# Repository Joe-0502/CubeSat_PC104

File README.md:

# CubeSat_PC104

Symbol and footprint libaraies in KiCAD need to be changed.

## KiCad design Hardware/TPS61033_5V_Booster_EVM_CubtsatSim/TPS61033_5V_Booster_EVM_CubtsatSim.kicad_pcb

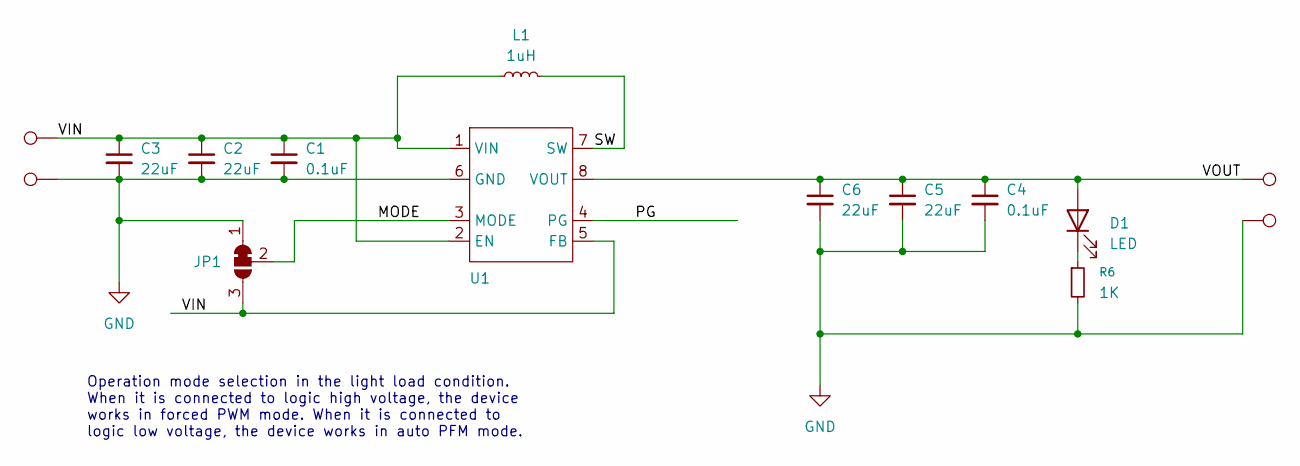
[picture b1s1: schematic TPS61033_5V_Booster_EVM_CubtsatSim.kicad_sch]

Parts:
C1, C4: 0.1uF; C_0603_1608Metric_Pad1.08x0.95mm_HandSolder
C2, C3, C5, C6: 22uF; C_0603_1608Metric_Pad1.08x0.95mm_HandSolder
D1: LED; LED_0603_1608Metric
JP1: SolderJumper_3_Bridged12; SolderJumper-3_P1.3mm_Open_RoundedPad1.0x1.5mm
L1: 1uH; IND_EXLA-0402_EAT
R6: 1K; R_0603_1608Metric_Pad0.98x0.95mm_HandSolder
TP1, TP2, TP3, TP4: TestPoint; TestPoint_THTPad_1.5x1.5mm_Drill0.7mm
U1: SOT-5X3

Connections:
/MODE: JP1.2 (C), U1.3 (MODE)
/PG: U1.4 (PG)
/SW: L1.2, U1.7 (SW)
/VIN: C1.1, C2.1, C3.1, JP1.3 (B), L1.1, TP1.1, U1.1 (VIN), U1.2 (EN), U1.5 (FB)
/VOUT: C4.1, C5.1, C6.1, D1.2 (A), TP3.1, U1.8 (VOUT)
GND: C1.2, C2.2, C3.2, C4.2, C5.2, C6.2, JP1.1 (A), R6.2, TP2.1, TP4.1, U1.6 (GND)
unnamed: D1.1 (K), R6.1

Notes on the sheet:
Operation mode selection in the light load condition. When it is connected to logic high voltage, the device works in forced PWM mode. When it is connected to logic low voltage, the device works in auto PFM mode.

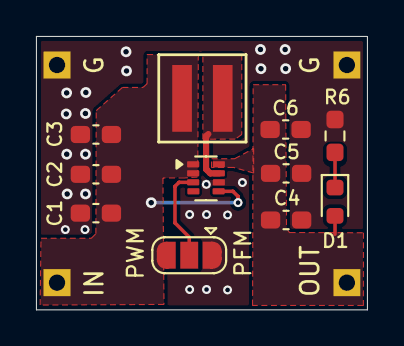
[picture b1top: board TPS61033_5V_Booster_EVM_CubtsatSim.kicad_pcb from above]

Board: 2 copper layers, 18.4 x 15.2 mm, 15 parts (0 on the bottom side), 6 nets.

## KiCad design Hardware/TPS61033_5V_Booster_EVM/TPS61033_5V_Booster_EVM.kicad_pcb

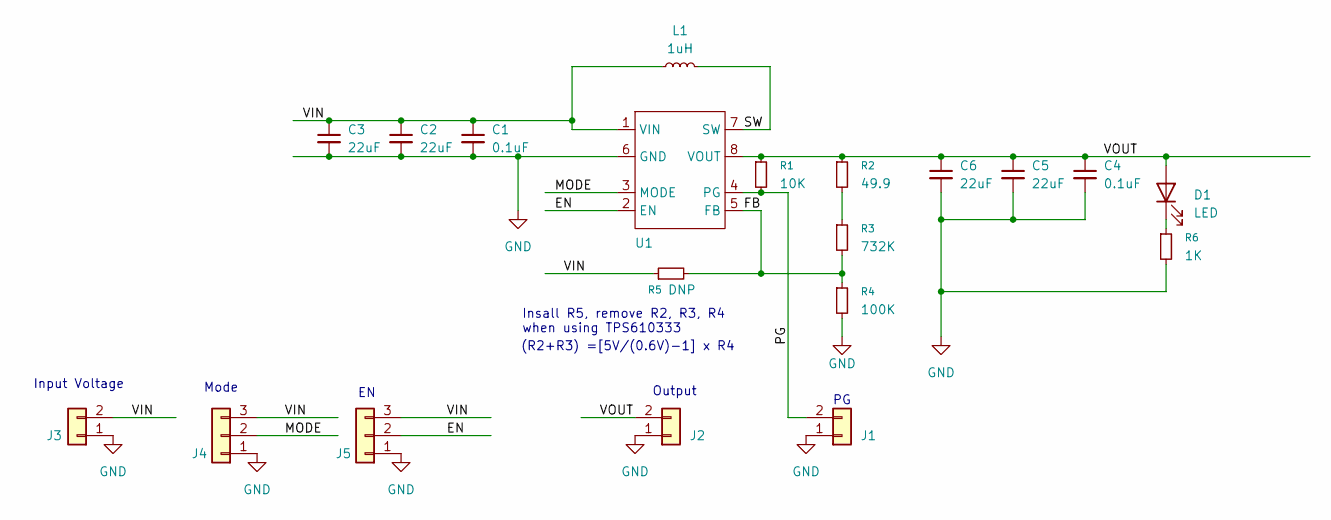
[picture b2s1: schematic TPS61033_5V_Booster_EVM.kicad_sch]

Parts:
C1, C4: 0.1uF; C_0805_2012Metric_Pad1.18x1.45mm_HandSolder
C2, C3, C5, C6: 22uF; C_0805_2012Metric_Pad1.18x1.45mm_HandSolder
D1: LED; LED_0603_1608Metric
J1, J2, J3: Conn_01x02; PinHeader_1x02_P2.54mm_Vertical
J4, J5: Conn_01x03; PinHeader_1x03_P2.54mm_Vertical
L1: 1uH; IND_EXLA-0402_EAT
R1: 10K; R_0603_1608Metric_Pad0.98x0.95mm_HandSolder
R2: 49.9; R_0603_1608Metric_Pad0.98x0.95mm_HandSolder
R3: 732K; R_0603_1608Metric_Pad0.98x0.95mm_HandSolder
R4: 100K; R_0603_1608Metric_Pad0.98x0.95mm_HandSolder
R5: DNP; R_0603_1608Metric_Pad0.98x0.95mm_HandSolder
R6: 1K; R_0603_1608Metric_Pad0.98x0.95mm_HandSolder
U1: SOT-5X3

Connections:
/EN: J5.2, U1.2 (EN)
/FB: R3.2, R4.1, R5.2, U1.5 (FB)
/MODE: J4.2, U1.3 (MODE)
/PG: J1.2, R1.2, U1.4 (PG)
/SW: L1.2, U1.7 (SW)
/VIN: C1.1, C2.1, C3.1, J3.2, J4.3, J5.3, L1.1, R5.1, U1.1 (VIN)
/VOUT: C4.1, C5.1, C6.1, D1.2 (A), J2.2, R1.1, R2.1, U1.8 (VOUT)
GND: C1.2, C2.2, C3.2, C4.2, C5.2, C6.2, J1.1, J2.1, J3.1, J4.1, J5.1, R4.2, R6.2, U1.6 (GND)
unnamed: D1.1 (K), R6.1
unnamed: R2.2, R3.1

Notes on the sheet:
(R2+R3) =[5V/(0.6V)-1] x R4
Output
Insall R5, remove R2, R3, R4 when using TPS610333
Input Voltage
Mode

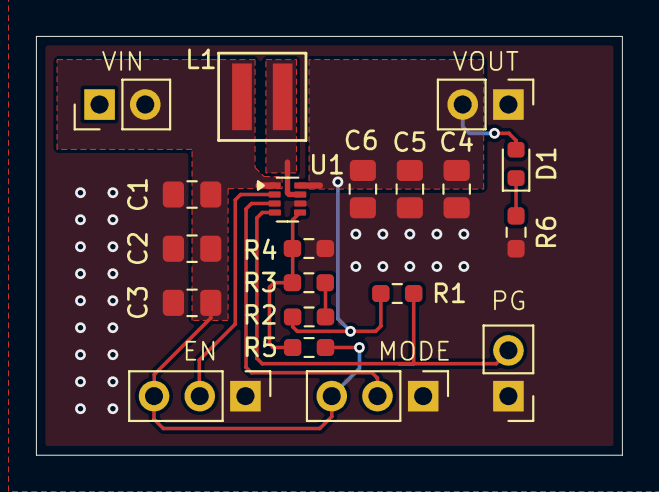
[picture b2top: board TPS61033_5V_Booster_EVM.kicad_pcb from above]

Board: 2 copper layers, 32.6 x 23.3 mm, 20 parts (0 on the bottom side), 10 nets.

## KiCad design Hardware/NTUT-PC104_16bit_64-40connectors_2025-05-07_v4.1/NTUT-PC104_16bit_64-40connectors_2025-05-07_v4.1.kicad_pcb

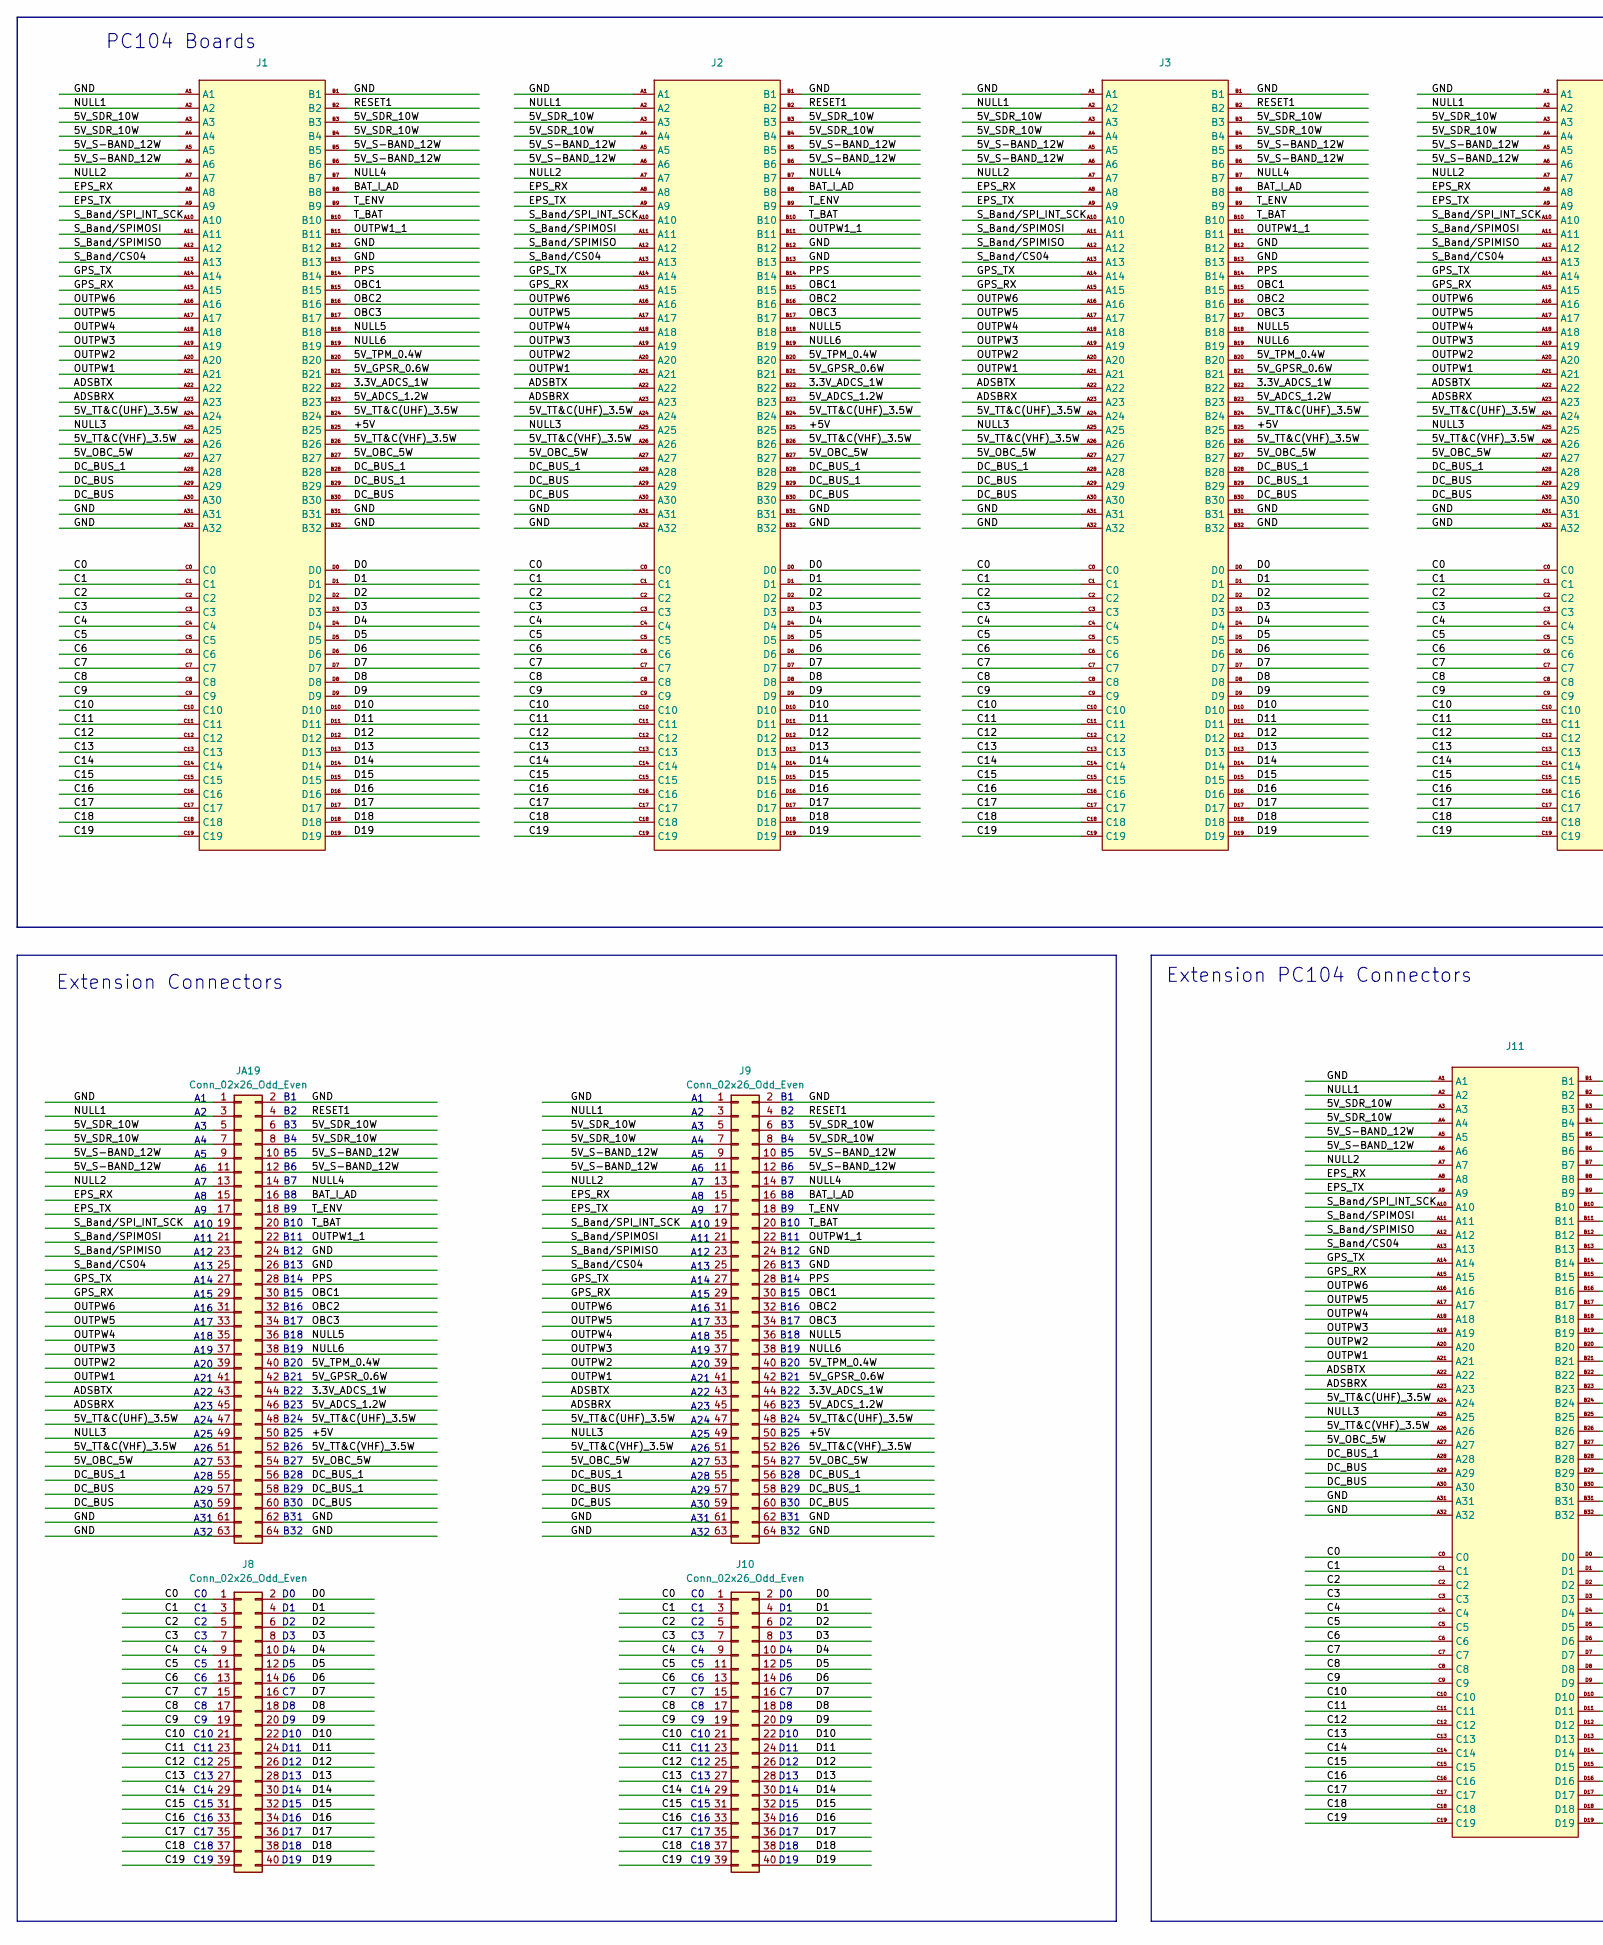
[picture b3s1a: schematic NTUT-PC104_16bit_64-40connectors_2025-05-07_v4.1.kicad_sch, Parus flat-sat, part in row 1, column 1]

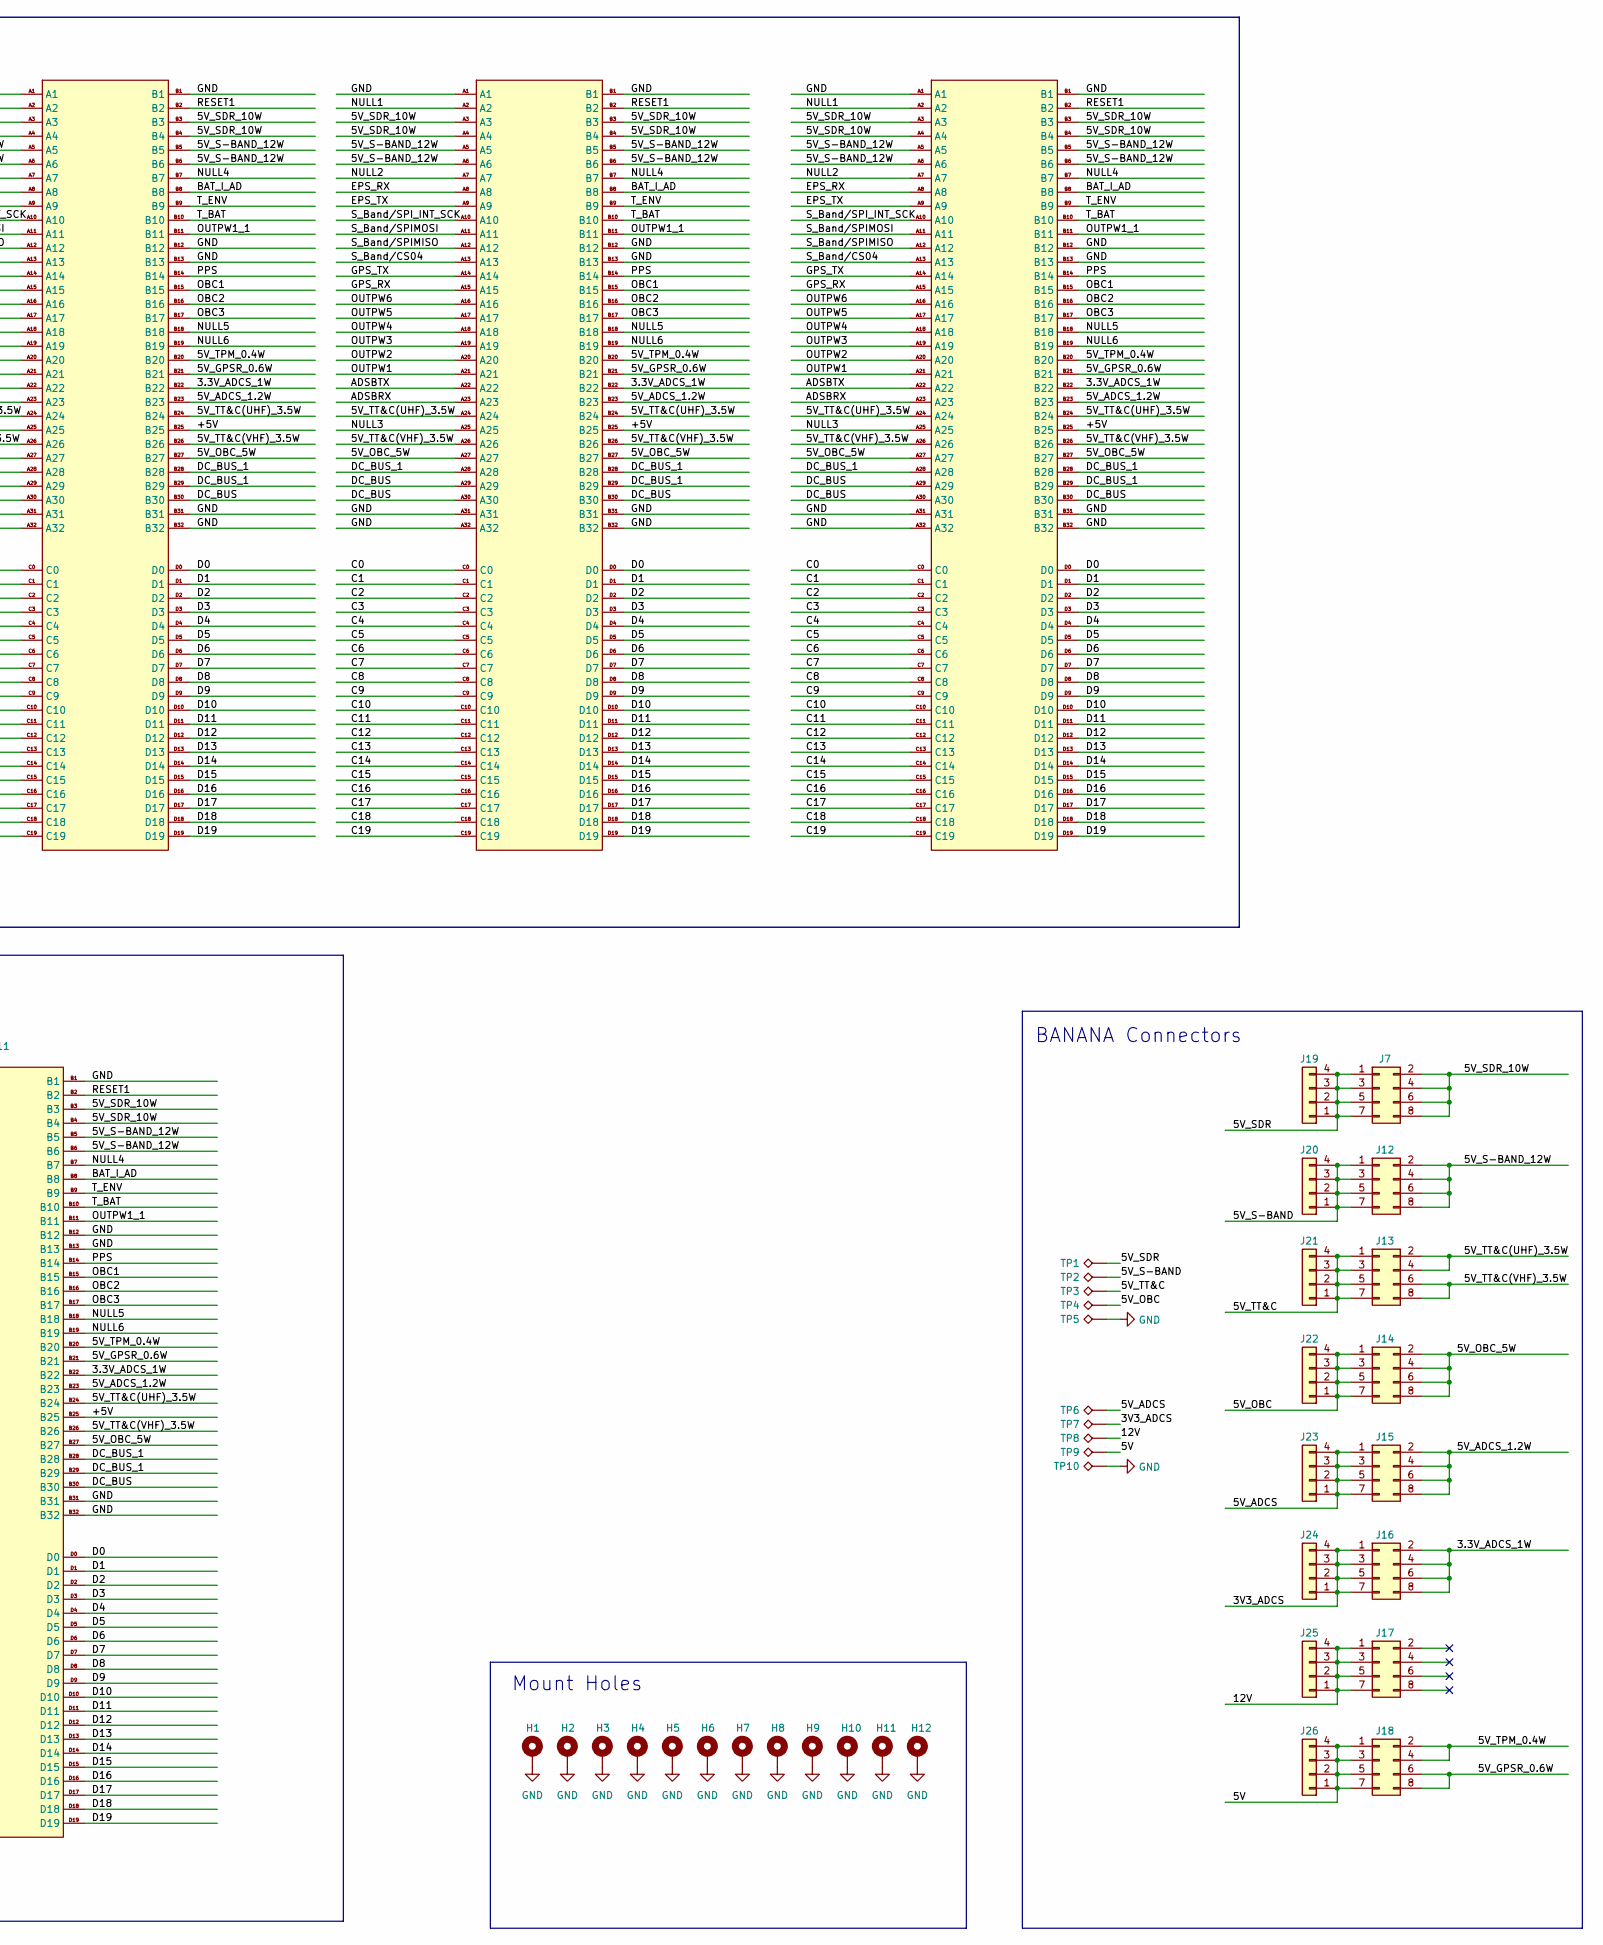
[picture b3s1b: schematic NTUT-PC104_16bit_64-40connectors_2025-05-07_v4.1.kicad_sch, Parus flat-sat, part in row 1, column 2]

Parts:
H1, H2, H3, H4, H5, H6, H7, H8, H9, H10, H11, H12: MountingHole_Pad; MountingHole_3.2mm_M3_Pad_Via
J1, J2, J3, J4, J5, J6: CubeSat_PC104_16bit_footprint
J7, J12, J13, J14, J15, J16, J17, J18: Conn_02x04_Odd_Even; PinHeader_2x04_P2.54mm_Vertical
J8, J10: Conn_02x26_Odd_Even; PinHeader_2x20_P2.54mm_Vertical
J9: Conn_02x26_Odd_Even; PinHeader_2x32_P2.54mm_Vertical
J11: PC104_16bit_Connector
J19, J20, J21, J22, J23, J24, J25, J26: Conn_01x04; PinHeader_1x04_P2.54mm_Vertical
JA19: Conn_02x26_Odd_Even; PinHeader_2x32_P2.54mm_Vertical
TP1, TP2, TP3, TP4, TP5, TP6, TP7, TP8, TP9, TP10: TestPoint_Alt; KSE_PN6095

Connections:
/3.3V_ADCS_1W: J1.B22, J2.B22, J3.B22, J4.B22, J5.B22, J6.B22, J9.44, J11.B22, J16.2, J16.4, J16.6, J16.8, JA19.44
/3V3_ADCS: J16.1, J16.3, J16.5, J16.7, J24.1, J24.2, J24.3, J24.4, TP7.1
/5V: J18.1, J18.3, J18.5, J18.7, J26.1, J26.2, J26.3, J26.4, TP9.1
/5V_ADCS: J15.1, J15.3, J15.5, J15.7, J23.1, J23.2, J23.3, J23.4, TP6.1
/5V_ADCS_1.2W: J1.B23, J2.B23, J3.B23, J4.B23, J5.B23, J6.B23, J9.46, J11.B23, J15.2, J15.4, J15.6, J15.8, JA19.46
/5V_GPSR_0.6W: J1.B21, J2.B21, J3.B21, J4.B21, J5.B21, J6.B21, J9.42, J11.B21, J18.6, J18.8, JA19.42
/5V_OBC: J14.1, J14.3, J14.5, J14.7, J22.1, J22.2, J22.3, J22.4, TP4.1
/5V_OBC_5W: J1.A27, J1.B27, J2.A27, J2.B27, J3.A27, J3.B27, J4.A27, J4.B27, J5.A27, J5.B27, J6.A27, J6.B27, J9.53, J9.54, J11.A27, J11.B27, J14.2, J14.4, J14.6, J14.8, JA19.53, JA19.54
/5V_S-BAND: J12.1, J12.3, J12.5, J12.7, J20.1, J20.2, J20.3, J20.4, TP2.1
/5V_S-BAND_12W: J1.A5, J1.A6, J1.B5, J1.B6, J2.A5, J2.A6, J2.B5, J2.B6, J3.A5, J3.A6, J3.B5, J3.B6, J4.A5, J4.A6, J4.B5, J4.B6, J5.A5, J5.A6, J5.B5, J5.B6, J6.A5, J6.A6, J6.B5, J6.B6, J9.9, J9.10, J9.11, J9.12, J11.A5, J11.A6, J11.B5, J11.B6, J12.2, J12.4, J12.6, J12.8, JA19.9, JA19.10, JA19.11, JA19.12
/5V_SDR: J7.1, J7.3, J7.5, J7.7, J19.1, J19.2, J19.3, J19.4, TP1.1
/5V_SDR_10W: J1.A3, J1.A4, J1.B3, J1.B4, J2.A3, J2.A4, J2.B3, J2.B4, J3.A3, J3.A4, J3.B3, J3.B4, J4.A3, J4.A4, J4.B3, J4.B4, J5.A3, J5.A4, J5.B3, J5.B4, J6.A3, J6.A4, J6.B3, J6.B4, J7.2, J7.4, J7.6, J7.8, J9.5, J9.6, J9.7, J9.8, J11.A3, J11.A4, J11.B3, J11.B4, JA19.5, JA19.6, JA19.7, JA19.8
/5V_TPM_0.4W: J1.B20, J2.B20, J3.B20, J4.B20, J5.B20, J6.B20, J9.40, J11.B20, J18.2, J18.4, JA19.40
/5V_TT&C: J13.1, J13.3, J13.5, J13.7, J21.1, J21.2, J21.3, J21.4, TP3.1
/5V_TT&C(UHF)_3.5W: J1.A24, J1.B24, J2.A24, J2.B24, J3.A24, J3.B24, J4.A24, J4.B24, J5.A24, J5.B24, J6.A24, J6.B24, J9.47, J9.48, J11.A24, J11.B24, J13.2, J13.4, JA19.47, JA19.48
/5V_TT&C(VHF)_3.5W: J1.A26, J1.B26, J2.A26, J2.B26, J3.A26, J3.B26, J4.A26, J4.B26, J5.A26, J5.B26, J6.A26, J6.B26, J9.51, J9.52, J11.A26, J11.B26, J13.6, J13.8, JA19.51, JA19.52
/12V: J17.1, J17.3, J17.5, J17.7, J25.1, J25.2, J25.3, J25.4, TP8.1
/+5V: J1.B25, J2.B25, J3.B25, J4.B25, J5.B25, J6.B25, J9.50, J11.B25, JA19.50
/ADSBRX: J1.A23, J2.A23, J3.A23, J4.A23, J5.A23, J6.A23, J9.45, J11.A23, JA19.45
/ADSBTX: J1.A22, J2.A22, J3.A22, J4.A22, J5.A22, J6.A22, J9.43, J11.A22, JA19.43
/BAT_I_AD: J1.B8, J2.B8, J3.B8, J4.B8, J5.B8, J6.B8, J9.16, J11.B8, JA19.16
/C0: J1.C0, J2.C0, J3.C0, J4.C0, J5.C0, J6.C0, J8.1, J10.1, J11.C0
/C1: J1.C1, J2.C1, J3.C1, J4.C1, J5.C1, J6.C1, J8.3, J10.3, J11.C1
/C2: J1.C2, J2.C2, J3.C2, J4.C2, J5.C2, J6.C2, J8.5, J10.5, J11.C2
/C3: J1.C3, J2.C3, J3.C3, J4.C3, J5.C3, J6.C3, J8.7, J10.7, J11.C3
/C4: J1.C4, J2.C4, J3.C4, J4.C4, J5.C4, J6.C4, J8.9, J10.9, J11.C4
/C5: J1.C5, J2.C5, J3.C5, J4.C5, J5.C5, J6.C5, J8.11, J10.11, J11.C5
/C6: J1.C6, J2.C6, J3.C6, J4.C6, J5.C6, J6.C6, J8.13, J10.13, J11.C6
/C7: J1.C7, J2.C7, J3.C7, J4.C7, J5.C7, J6.C7, J8.15, J10.15, J11.C7
/C8: J1.C8, J2.C8, J3.C8, J4.C8, J5.C8, J6.C8, J8.17, J10.17, J11.C8
/C9: J1.C9, J2.C9, J3.C9, J4.C9, J5.C9, J6.C9, J8.19, J10.19, J11.C9
/C10: J1.C10, J2.C10, J3.C10, J4.C10, J5.C10, J6.C10, J8.21, J10.21, J11.C10
/C11: J1.C11, J2.C11, J3.C11, J4.C11, J5.C11, J6.C11, J8.23, J10.23, J11.C11
/C12: J1.C12, J2.C12, J3.C12, J4.C12, J5.C12, J6.C12, J8.25, J10.25, J11.C12
/C13: J1.C13, J2.C13, J3.C13, J4.C13, J5.C13, J6.C13, J8.27, J10.27, J11.C13
/C14: J1.C14, J2.C14, J3.C14, J4.C14, J5.C14, J6.C14, J8.29, J10.29, J11.C14
/C15: J1.C15, J2.C15, J3.C15, J4.C15, J5.C15, J6.C15, J8.31, J10.31, J11.C15
/C16: J1.C16, J2.C16, J3.C16, J4.C16, J5.C16, J6.C16, J8.33, J10.33, J11.C16
/C17: J1.C17, J2.C17, J3.C17, J4.C17, J5.C17, J6.C17, J8.35, J10.35, J11.C17
/C18: J1.C18, J2.C18, J3.C18, J4.C18, J5.C18, J6.C18, J8.37, J10.37, J11.C18
/C19: J1.C19, J2.C19, J3.C19, J4.C19, J5.C19, J6.C19, J8.39, J10.39, J11.C19
/D0: J1.D0, J2.D0, J3.D0, J4.D0, J5.D0, J6.D0, J8.2, J10.2, J11.D0
/D1: J1.D1, J2.D1, J3.D1, J4.D1, J5.D1, J6.D1, J8.4, J10.4, J11.D1
/D2: J1.D2, J2.D2, J3.D2, J4.D2, J5.D2, J6.D2, J8.6, J10.6, J11.D2
/D3: J1.D3, J2.D3, J3.D3, J4.D3, J5.D3, J6.D3, J8.8, J10.8, J11.D3
/D4: J1.D4, J2.D4, J3.D4, J4.D4, J5.D4, J6.D4, J8.10, J10.10, J11.D4
/D5: J1.D5, J2.D5, J3.D5, J4.D5, J5.D5, J6.D5, J8.12, J10.12, J11.D5
/D6: J1.D6, J2.D6, J3.D6, J4.D6, J5.D6, J6.D6, J8.14, J10.14, J11.D6
/D7: J1.D7, J2.D7, J3.D7, J4.D7, J5.D7, J6.D7, J8.16, J10.16, J11.D7
/D8: J1.D8, J2.D8, J3.D8, J4.D8, J5.D8, J6.D8, J8.18, J10.18, J11.D8
/D9: J1.D9, J2.D9, J3.D9, J4.D9, J5.D9, J6.D9, J8.20, J10.20, J11.D9
/D10: J1.D10, J2.D10, J3.D10, J4.D10, J5.D10, J6.D10, J8.22, J10.22, J11.D10
/D11: J1.D11, J2.D11, J3.D11, J4.D11, J5.D11, J6.D11, J8.24, J10.24, J11.D11
/D12: J1.D12, J2.D12, J3.D12, J4.D12, J5.D12, J6.D12, J8.26, J10.26, J11.D12
/D13: J1.D13, J2.D13, J3.D13, J4.D13, J5.D13, J6.D13, J8.28, J10.28, J11.D13
/D14: J1.D14, J2.D14, J3.D14, J4.D14, J5.D14, J6.D14, J8.30, J10.30, J11.D14
/D15: J1.D15, J2.D15, J3.D15, J4.D15, J5.D15, J6.D15, J8.32, J10.32, J11.D15
/D16: J1.D16, J2.D16, J3.D16, J4.D16, J5.D16, J6.D16, J8.34, J10.34, J11.D16
/D17: J1.D17, J2.D17, J3.D17, J4.D17, J5.D17, J6.D17, J8.36, J10.36, J11.D17
/D18: J1.D18, J2.D18, J3.D18, J4.D18, J5.D18, J6.D18, J8.38, J10.38, J11.D18
/D19: J1.D19, J2.D19, J3.D19, J4.D19, J5.D19, J6.D19, J8.40, J10.40, J11.D19
/DC_BUS: J1.A29, J1.A30, J1.B30, J2.A29, J2.A30, J2.B30, J3.A29, J3.A30, J3.B30, J4.A29, J4.A30, J4.B30, J5.A29, J5.A30, J5.B30, J6.A29, J6.A30, J6.B30, J9.57, J9.59, J9.60, J11.A29, J11.A30, J11.B30, JA19.57, JA19.59, JA19.60
/DC_BUS_1: J1.A28, J1.B28, J1.B29, J2.A28, J2.B28, J2.B29, J3.A28, J3.B28, J3.B29, J4.A28, J4.B28, J4.B29, J5.A28, J5.B28, J5.B29, J6.A28, J6.B28, J6.B29, J9.55, J9.56, J9.58, J11.A28, J11.B28, J11.B29, JA19.55, JA19.56, JA19.58
/EPS_RX: J1.A8, J2.A8, J3.A8, J4.A8, J5.A8, J6.A8, J9.15, J11.A8, JA19.15
/EPS_TX: J1.A9, J2.A9, J3.A9, J4.A9, J5.A9, J6.A9, J9.17, J11.A9, JA19.17
/GPS_RX: J1.A15, J2.A15, J3.A15, J4.A15, J5.A15, J6.A15, J9.29, J11.A15, JA19.29
/GPS_TX: J1.A14, J2.A14, J3.A14, J4.A14, J5.A14, J6.A14, J9.27, J11.A14, JA19.27
/NULL1: J1.A2, J2.A2, J3.A2, J4.A2, J5.A2, J6.A2, J9.3, J11.A2, JA19.3
/NULL2: J1.A7, J2.A7, J3.A7, J4.A7, J5.A7, J6.A7, J9.13, J11.A7, JA19.13
/NULL3: J1.A25, J2.A25, J3.A25, J4.A25, J5.A25, J6.A25, J9.49, J11.A25, JA19.49
/NULL4: J1.B7, J2.B7, J3.B7, J4.B7, J5.B7, J6.B7, J9.14, J11.B7, JA19.14
/NULL5: J1.B18, J2.B18, J3.B18, J4.B18, J5.B18, J6.B18, J9.36, J11.B18, JA19.36
/NULL6: J1.B19, J2.B19, J3.B19, J4.B19, J5.B19, J6.B19, J9.38, J11.B19, JA19.38
/OBC1: J1.B15, J2.B15, J3.B15, J4.B15, J5.B15, J6.B15, J9.30, J11.B15, JA19.30
/OBC2: J1.B16, J2.B16, J3.B16, J4.B16, J5.B16, J6.B16, J9.32, J11.B16, JA19.32
/OBC3: J1.B17, J2.B17, J3.B17, J4.B17, J5.B17, J6.B17, J9.34, J11.B17, JA19.34
/OUTPW1: J1.A21, J2.A21, J3.A21, J4.A21, J5.A21, J6.A21, J9.41, J11.A21, JA19.41
/OUTPW1_1: J1.B11, J2.B11, J3.B11, J4.B11, J5.B11, J6.B11, J9.22, J11.B11, JA19.22
/OUTPW2: J1.A20, J2.A20, J3.A20, J4.A20, J5.A20, J6.A20, J9.39, J11.A20, JA19.39
/OUTPW3: J1.A19, J2.A19, J3.A19, J4.A19, J5.A19, J6.A19, J9.37, J11.A19, JA19.37
/OUTPW4: J1.A18, J2.A18, J3.A18, J4.A18, J5.A18, J6.A18, J9.35, J11.A18, JA19.35
/OUTPW5: J1.A17, J2.A17, J3.A17, J4.A17, J5.A17, J6.A17, J9.33, J11.A17, JA19.33
/OUTPW6: J1.A16, J2.A16, J3.A16, J4.A16, J5.A16, J6.A16, J9.31, J11.A16, JA19.31
/PPS: J1.B14, J2.B14, J3.B14, J4.B14, J5.B14, J6.B14, J9.28, J11.B14, JA19.28
/RESET1: J1.B2, J2.B2, J3.B2, J4.B2, J5.B2, J6.B2, J9.4, J11.B2, JA19.4
/S_Band/CS04: J1.A13, J2.A13, J3.A13, J4.A13, J5.A13, J6.A13, J9.25, J11.A13, JA19.25
/S_Band/SPIMISO: J1.A12, J2.A12, J3.A12, J4.A12, J5.A12, J6.A12, J9.23, J11.A12, JA19.23
/S_Band/SPIMOSI: J1.A11, J2.A11, J3.A11, J4.A11, J5.A11, J6.A11, J9.21, J11.A11, JA19.21
/S_Band/SPI_INT_SCK: J1.A10, J2.A10, J3.A10, J4.A10, J5.A10, J6.A10, J9.19, J11.A10, JA19.19
/T_BAT: J1.B10, J2.B10, J3.B10, J4.B10, J5.B10, J6.B10, J9.20, J11.B10, JA19.20
/T_ENV: J1.B9, J2.B9, J3.B9, J4.B9, J5.B9, J6.B9, J9.18, J11.B9, JA19.18
GND: H1.1, H2.1, H3.1, H4.1, H5.1, H6.1, H7.1, H8.1, H9.1, H10.1, H11.1, H12.1, J1.A1, J1.A31, J1.A32, J1.B1, J1.B12, J1.B13, J1.B31, J1.B32, J2.A1, J2.A31, J2.A32, J2.B1, J2.B12, J2.B13, J2.B31, J2.B32, J3.A1, J3.A31, J3.A32, J3.B1, J3.B12, J3.B13, J3.B31, J3.B32, J4.A1, J4.A31, J4.A32, J4.B1, J4.B12, J4.B13, J4.B31, J4.B32, J5.A1, J5.A31, J5.A32, J5.B1, J5.B12, J5.B13, J5.B31, J5.B32, J6.A1, J6.A31, J6.A32, J6.B1, J6.B12, J6.B13, J6.B31, J6.B32, J9.1, J9.2, J9.24, J9.26, J9.61, J9.62, J9.63, J9.64, J11.A1, J11.A31, J11.A32, J11.B1, J11.B12, J11.B13, J11.B31, J11.B32, JA19.1, JA19.2, JA19.24, JA19.26, JA19.61, JA19.62, JA19.63, JA19.64, TP5.1, TP10.1

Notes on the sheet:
D15
B14
D10
B30
D11
A29
A13
B18
C19
C12
C16
A19
C14
A31
A26
A21
B15
B10
Extension Connectors
A11
B12
C18
A17
B21
A30
Extension PC104 Connectors
B17
B22
B11
B25
C10
C11
B27
D17
B13
A14
C13
D12
B26
B24

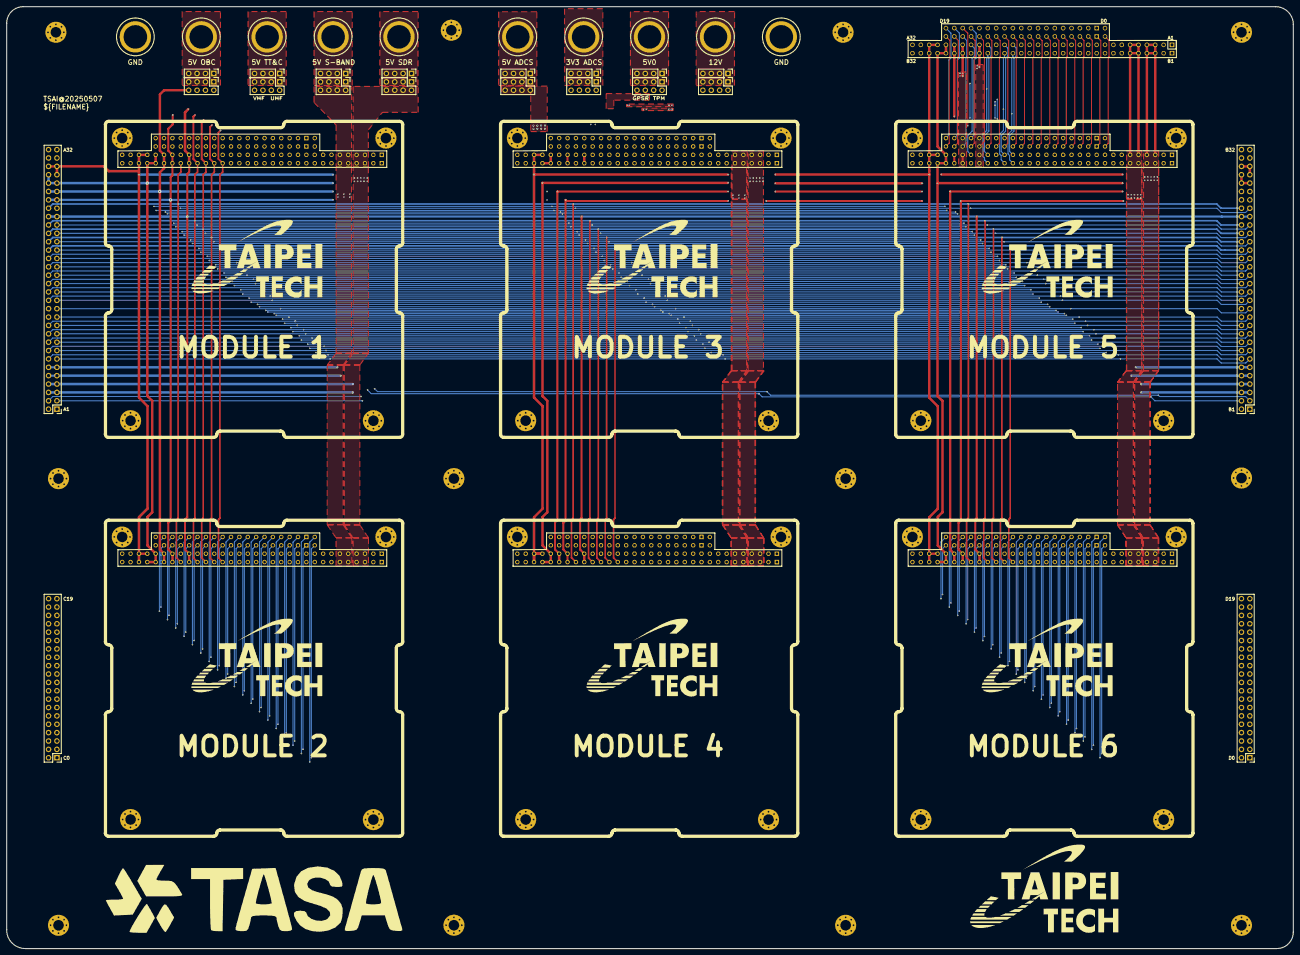
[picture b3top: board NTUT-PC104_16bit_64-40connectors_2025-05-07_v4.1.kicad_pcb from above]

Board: 4 copper layers, 390.3 x 285.7 mm, 49 parts (0 on the bottom side), 92 nets.

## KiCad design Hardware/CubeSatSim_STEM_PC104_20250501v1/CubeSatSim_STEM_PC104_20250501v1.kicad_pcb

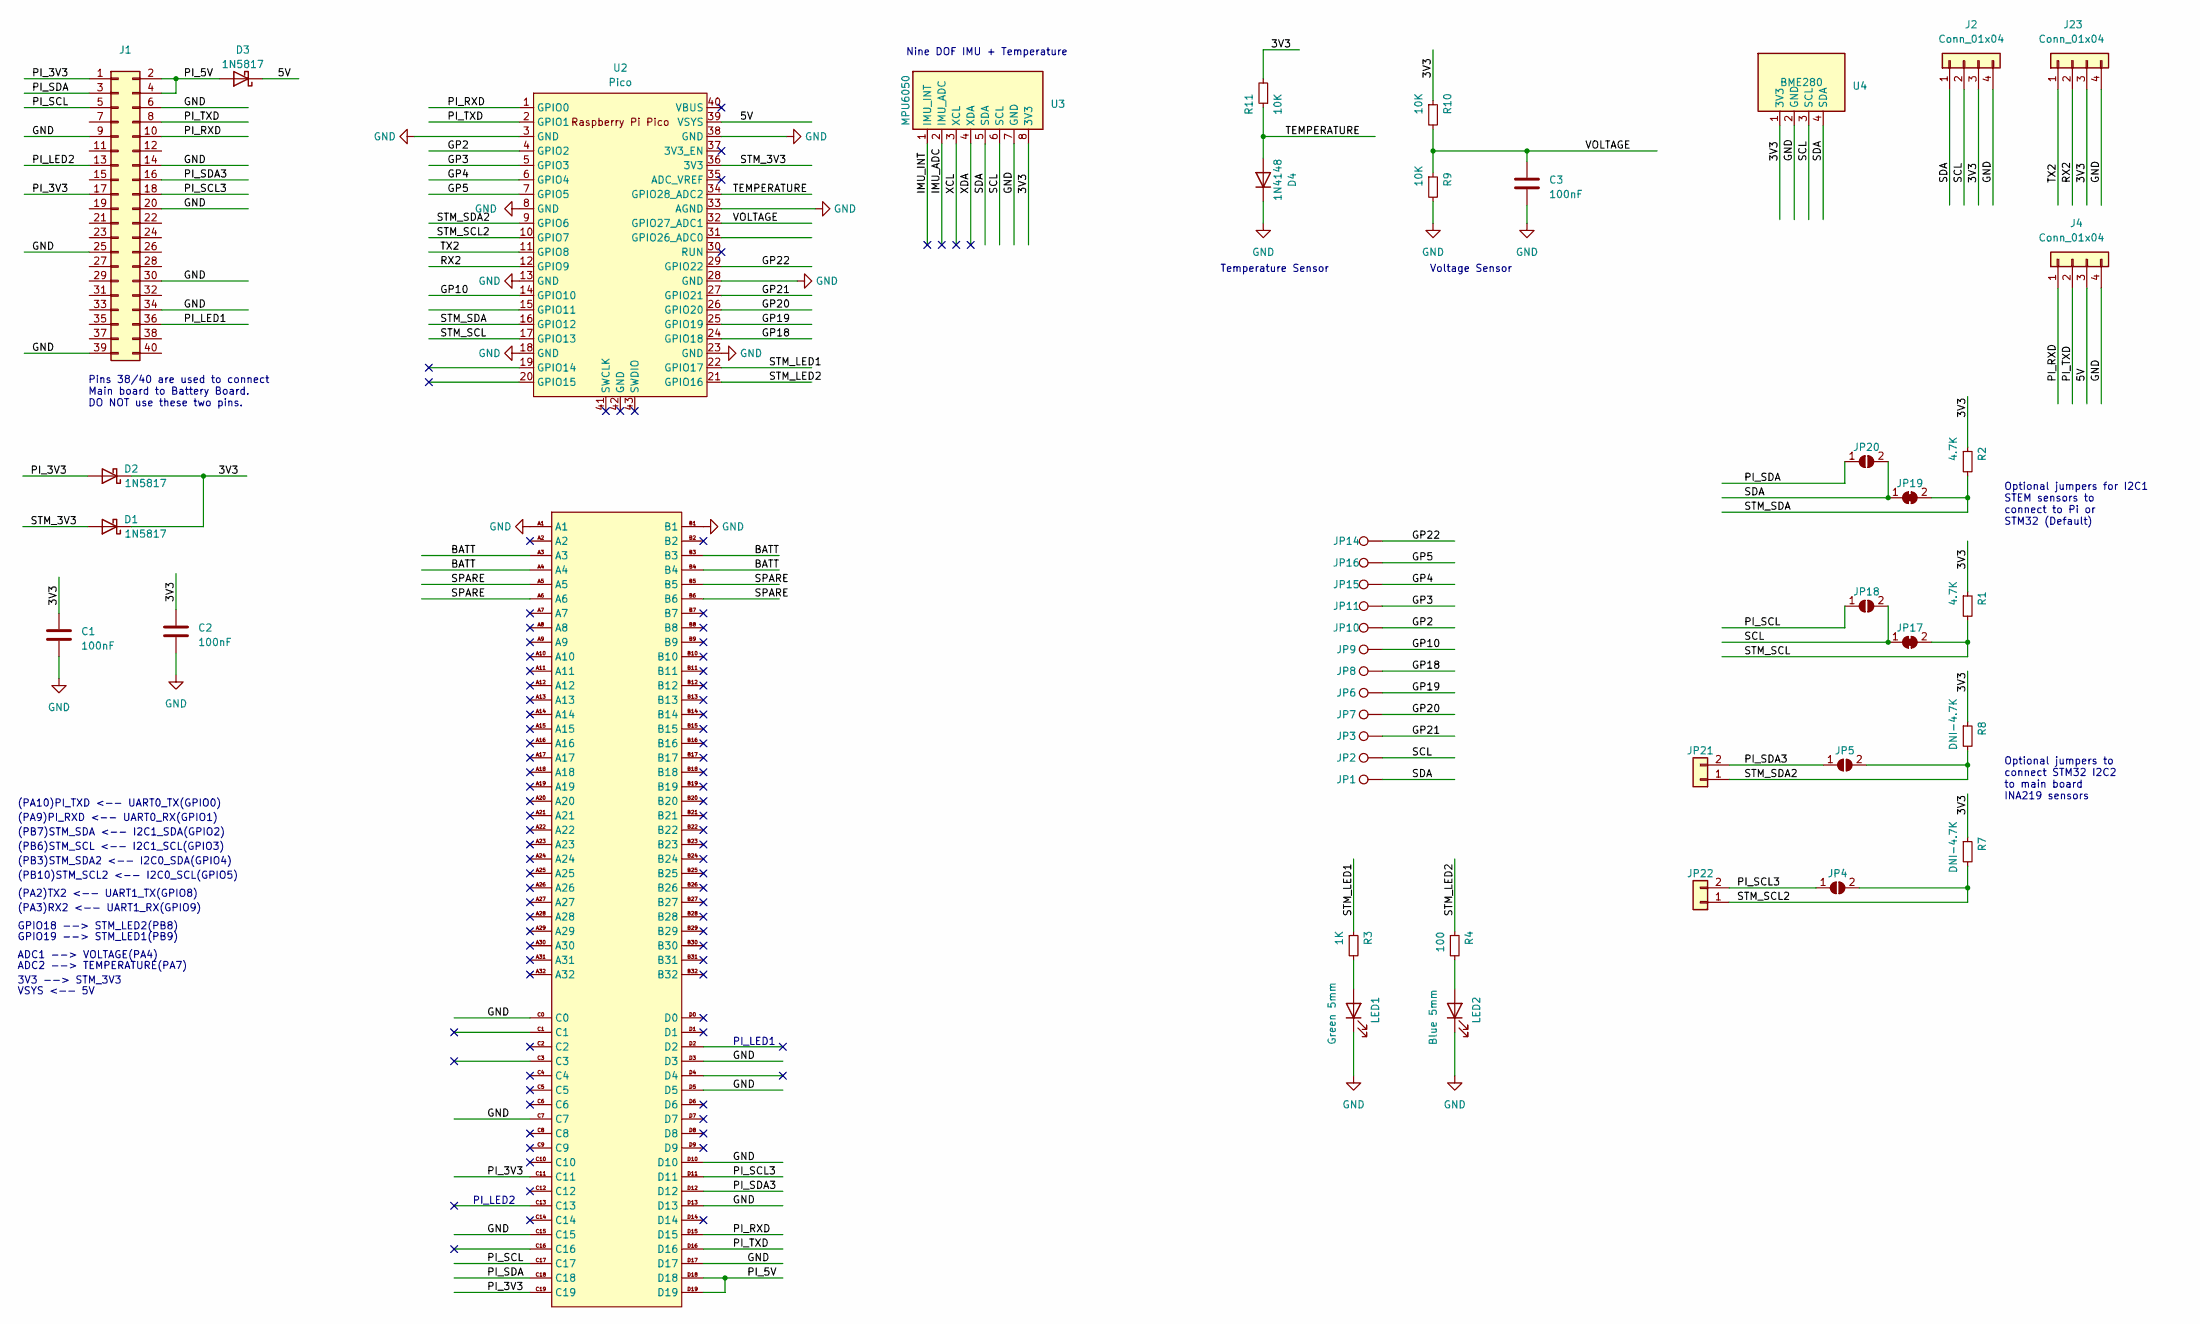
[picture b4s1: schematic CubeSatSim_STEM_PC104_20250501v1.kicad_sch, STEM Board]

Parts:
C1, C2, C3: 100nF; AMSAT_C_TH_5.08
D1, D2, D3: 1N5817; 1N5817_TH_100mil
D4: 1N4148; 1N5817_TH_100mil
J1: Conn_02x20_Odd_Even; PinHeader_2x20_P2.54mm_Vertical
J2, J4, J23: Conn_01x04; PinHeader_1x04_P2.54mm_Vertical
J3: CubeSat_PC104_16bit_footprint_Edge.Cut
JP1, JP2, JP3, JP6, JP7, JP8, JP9, JP10, JP11, JP14, JP15, JP16: TestPoint; Test_Point_Vertical_S
JP4, JP5, JP18, JP20: SolderJumper_2_Open; SolderJumper-2_P1.3mm_Open_Pad1.0x1.5mm
JP17, JP19: SolderJumper_2_Bridged; SolderJumper-2_P1.3mm_Bridged_Pad1.0x1.5mm
JP21, JP22: Conn_01x02; PinHeader_1x02_P2.54mm_Vertical
LED1: Green 5mm; LED_D3.0mm
LED2: Blue 5mm; LED_D3.0mm
R1, R2: 4.7K; R_TH_V_2.54
R3: 1K; R_TH_V_2.54
R4: 100; R_TH_V_2.54
R7, R8: DNI-4.7K; R_TH_V_2.54
R9, R10, R11: 10K; R_TH_V_2.54
U2: Pico; RPi_Pico_TH
U3: MPU6050; MPU6050_IMU_Module
U4: BME280; BME280_Module

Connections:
/3V3: C1.1, C2.1, D1.1 (K), D2.1 (K), J2.3, J23.3, R1.1, R2.1, R7.1, R8.1, R10.1, R11.2, U3.8 (3V3), U4.1 (3V3)
/5V: D3.1 (K), J4.3, U2.39 (VSYS)
/BATT: J3.A3, J3.A4, J3.B3, J3.B4
/GP2: JP10.1, U2.4 (GPIO2)
/GP3: JP11.1, U2.5 (GPIO3)
/GP4: JP15.1, U2.6 (GPIO4)
/GP5: JP16.1, U2.7 (GPIO5)
/GP10: JP9.1, U2.14 (GPIO10)
/GP18: JP8.1, U2.24 (GPIO18)
/GP19: JP6.1, U2.25 (GPIO19)
/GP20: JP7.1, U2.26 (GPIO20)
/GP21: JP3.1, U2.27 (GPIO21)
/GP22: JP14.1, U2.29 (GPIO22)
/IMU_ADC: U3.2 (IMU_ADC)
/IMU_INT: U3.1 (IMU_INT)
/PI_3V3: D2.2 (A), J1.1, J1.17, J3.C11, J3.C19
/PI_5V: D3.2 (A), J1.2, J1.4, J3.D18, J3.D19
/PI_LED1: J1.36
/PI_LED2: J1.13
/PI_RXD: J1.10, J3.D15, J4.1, U2.1 (GPIO0)
/PI_SCL: J1.5, J3.C17, JP18.1 (A)
/PI_SCL3: J1.18, J3.D11, JP4.1 (A), JP22.2
/PI_SDA: J1.3, J3.C18, JP20.1 (A)
/PI_SDA3: J1.16, J3.D12, JP5.1 (A), JP21.2
/PI_TXD: J1.8, J3.D16, J4.2, U2.2 (GPIO1)
/RX2: J23.2, U2.12 (GPIO9)
/SCL: J2.2, JP2.1, JP17.1 (A), JP18.2 (B), U3.6 (SCL), U4.3 (SCL)
/SDA: J2.1, JP1.1, JP19.1 (A), JP20.2 (B), U3.5 (SDA), U4.4 (SDA)
/SPARE: J3.A5, J3.A6, J3.B5, J3.B6
/STM_3V3: D1.2 (A), U2.36 (3V3)
/STM_LED1: R3.1, U2.22 (GPIO17)
/STM_LED2: R4.1, U2.21 (GPIO16)
/STM_SCL: JP17.2 (B), R1.2, U2.17 (GPIO13)
/STM_SCL2: JP4.2 (B), JP22.1, R7.2, U2.10 (GPIO7)
/STM_SDA: JP19.2 (B), R2.2, U2.16 (GPIO12)
/STM_SDA2: JP5.2 (B), JP21.1, R8.2, U2.9 (GPIO6)
/TEMPERATURE: D4.2 (A), R11.1, U2.34 (GPIO28_ADC2)
/TX2: J23.1, U2.11 (GPIO8)
/VOLTAGE: C3.2, R9.1, R10.2, U2.32 (GPIO27_ADC1)
/XCL: U3.3 (XCL)
/XDA: U3.4 (XDA)
GND: C1.2, C2.2, C3.1, D4.1 (K), J1.6, J1.9, J1.14, J1.20, J1.25, J1.30, J1.34, J1.39, J2.4, J3.A1, J3.B1, J3.C0, J3.C7, J3.C15, J3.D3, J3.D5, J3.D10, J3.D13, J3.D17, J4.4, J23.4, LED1.1 (K), LED2.1 (K), R9.2, U2.3 (GND), U2.8 (GND), U2.13 (GND), U2.18 (GND), U2.23 (GND), U2.28 (GND), U2.33 (AGND), U2.38 (GND), U3.7 (GND), U4.2 (GND)
unnamed: LED1.2 (A), R3.2
unnamed: LED2.2 (A), R4.2

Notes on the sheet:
(PB3)STM_SDA2 <-- I2C0_SDA(GPIO4)
(PB7)STM_SDA <-- I2C1_SDA(GPIO2)
PI_LED2
Temperature Sensor
VSYS <-- 5V
(PA2)TX2 <-- UART1_TX(GPIO8)
3V3 --> STM_3V3
GPIO19 --> STM_LED1(PB9)
Pins 38/40 are used to connect Main board to Battery Board. DO NOT use these two pins.
PI_LED1
Optional jumpers to connect STM32 I2C2 to main board INA219 sensors
(PB6)STM_SCL <-- I2C1_SCL(GPIO3)
(PB10)STM_SCL2 <-- I2C0_SCL(GPIO5)
(PA9)PI_RXD <-- UART0_RX(GPIO1)
Optional jumpers for I2C1 STEM sensors to connect to Pi or STM32 (Default)
(PA10)PI_TXD <-- UART0_TX(GPIO0)
(PA3)RX2 <-- UART1_RX(GPIO9)
ADC2 --> TEMPERATURE(PA7)
GPIO18 --> STM_LED2(PB8)
Voltage Sensor
Nine DOF IMU + Temperature
ADC1 --> VOLTAGE(PA4)

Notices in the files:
Hardware/CubeSatSim_STEM_PC104_20250501v1/CubeSatSim_STEM_PC104_20250501v1.kicad_pcb:
(c) CC-BY-NC-SA+ - 2019-2022 AMSAT
